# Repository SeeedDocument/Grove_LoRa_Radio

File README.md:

# Grove_LoRa_Radio
Grove LoRa Radio 433MHz SKU: 113060007

Grove LoRa Radio 868MHz SKU: 113060006

Change Log:

- 2016-11-27: create repos by Jiankai.li (jiankai.li@seeed.cc)

## About Seeed

Seeed is a hardware innovation platform for makers to grow inspirations into differentiating products. By working closely with technology providers of all scale, Seeed provides accessible technologies with quality, speed and supply chain knowledge. When prototypes are ready to iterate, Seeed helps productize 1 to 1,000 pcs using in-house engineering, supply chain management and agile manufacture forces. Seeed also team up with incubators, Chinese tech ecosystem, investors and distribution channels to portal Maker startups beyond.

## Contribution

We warmly welcome contribution to this documentation project. You can do this basically by [forking](https://help.github.com/articles/fork-a-repo), committing modifications and then [pulling requests](https://help.github.com/articles/using-pull-requests) (follow the links above for operating guide). Adding change log and your contact into file header is encouraged. Thanks for your contribution.

LICENSE
-------
Copyright (c) 2008-2016 Seeed Development Limited (www.seeedstudio.com / www.seeed.cc)

### Documents and Images
</a><br />
This work (product documents and associated images) are licensed under a <a rel="license" href="http://creativecommons.org/licenses/by-sa/4.0/">Creative Commons Attribution-ShareAlike 4.0 International License</a>. 

### Software Library
All demo software, code examples embedded in the document and any software libraray provided with the product document are licensed under [MIT License](https://github.com/SeeedDoc/WikiMigrationSync/blob/master/MIT_LICENSE "MIT LICENSE") unless otherwise specified.

### Thirdparty content
The resources provided with the product documents also contains datasheets, software examples and other content copyrighted by 3rd party authors and companies. All such items are copyright of respective owners. The use of such items are governed by their respective licenses.

All trademarks are the property of their respective owners.

### To Contact

Write to us at  with subject line "Wiki". Thanks

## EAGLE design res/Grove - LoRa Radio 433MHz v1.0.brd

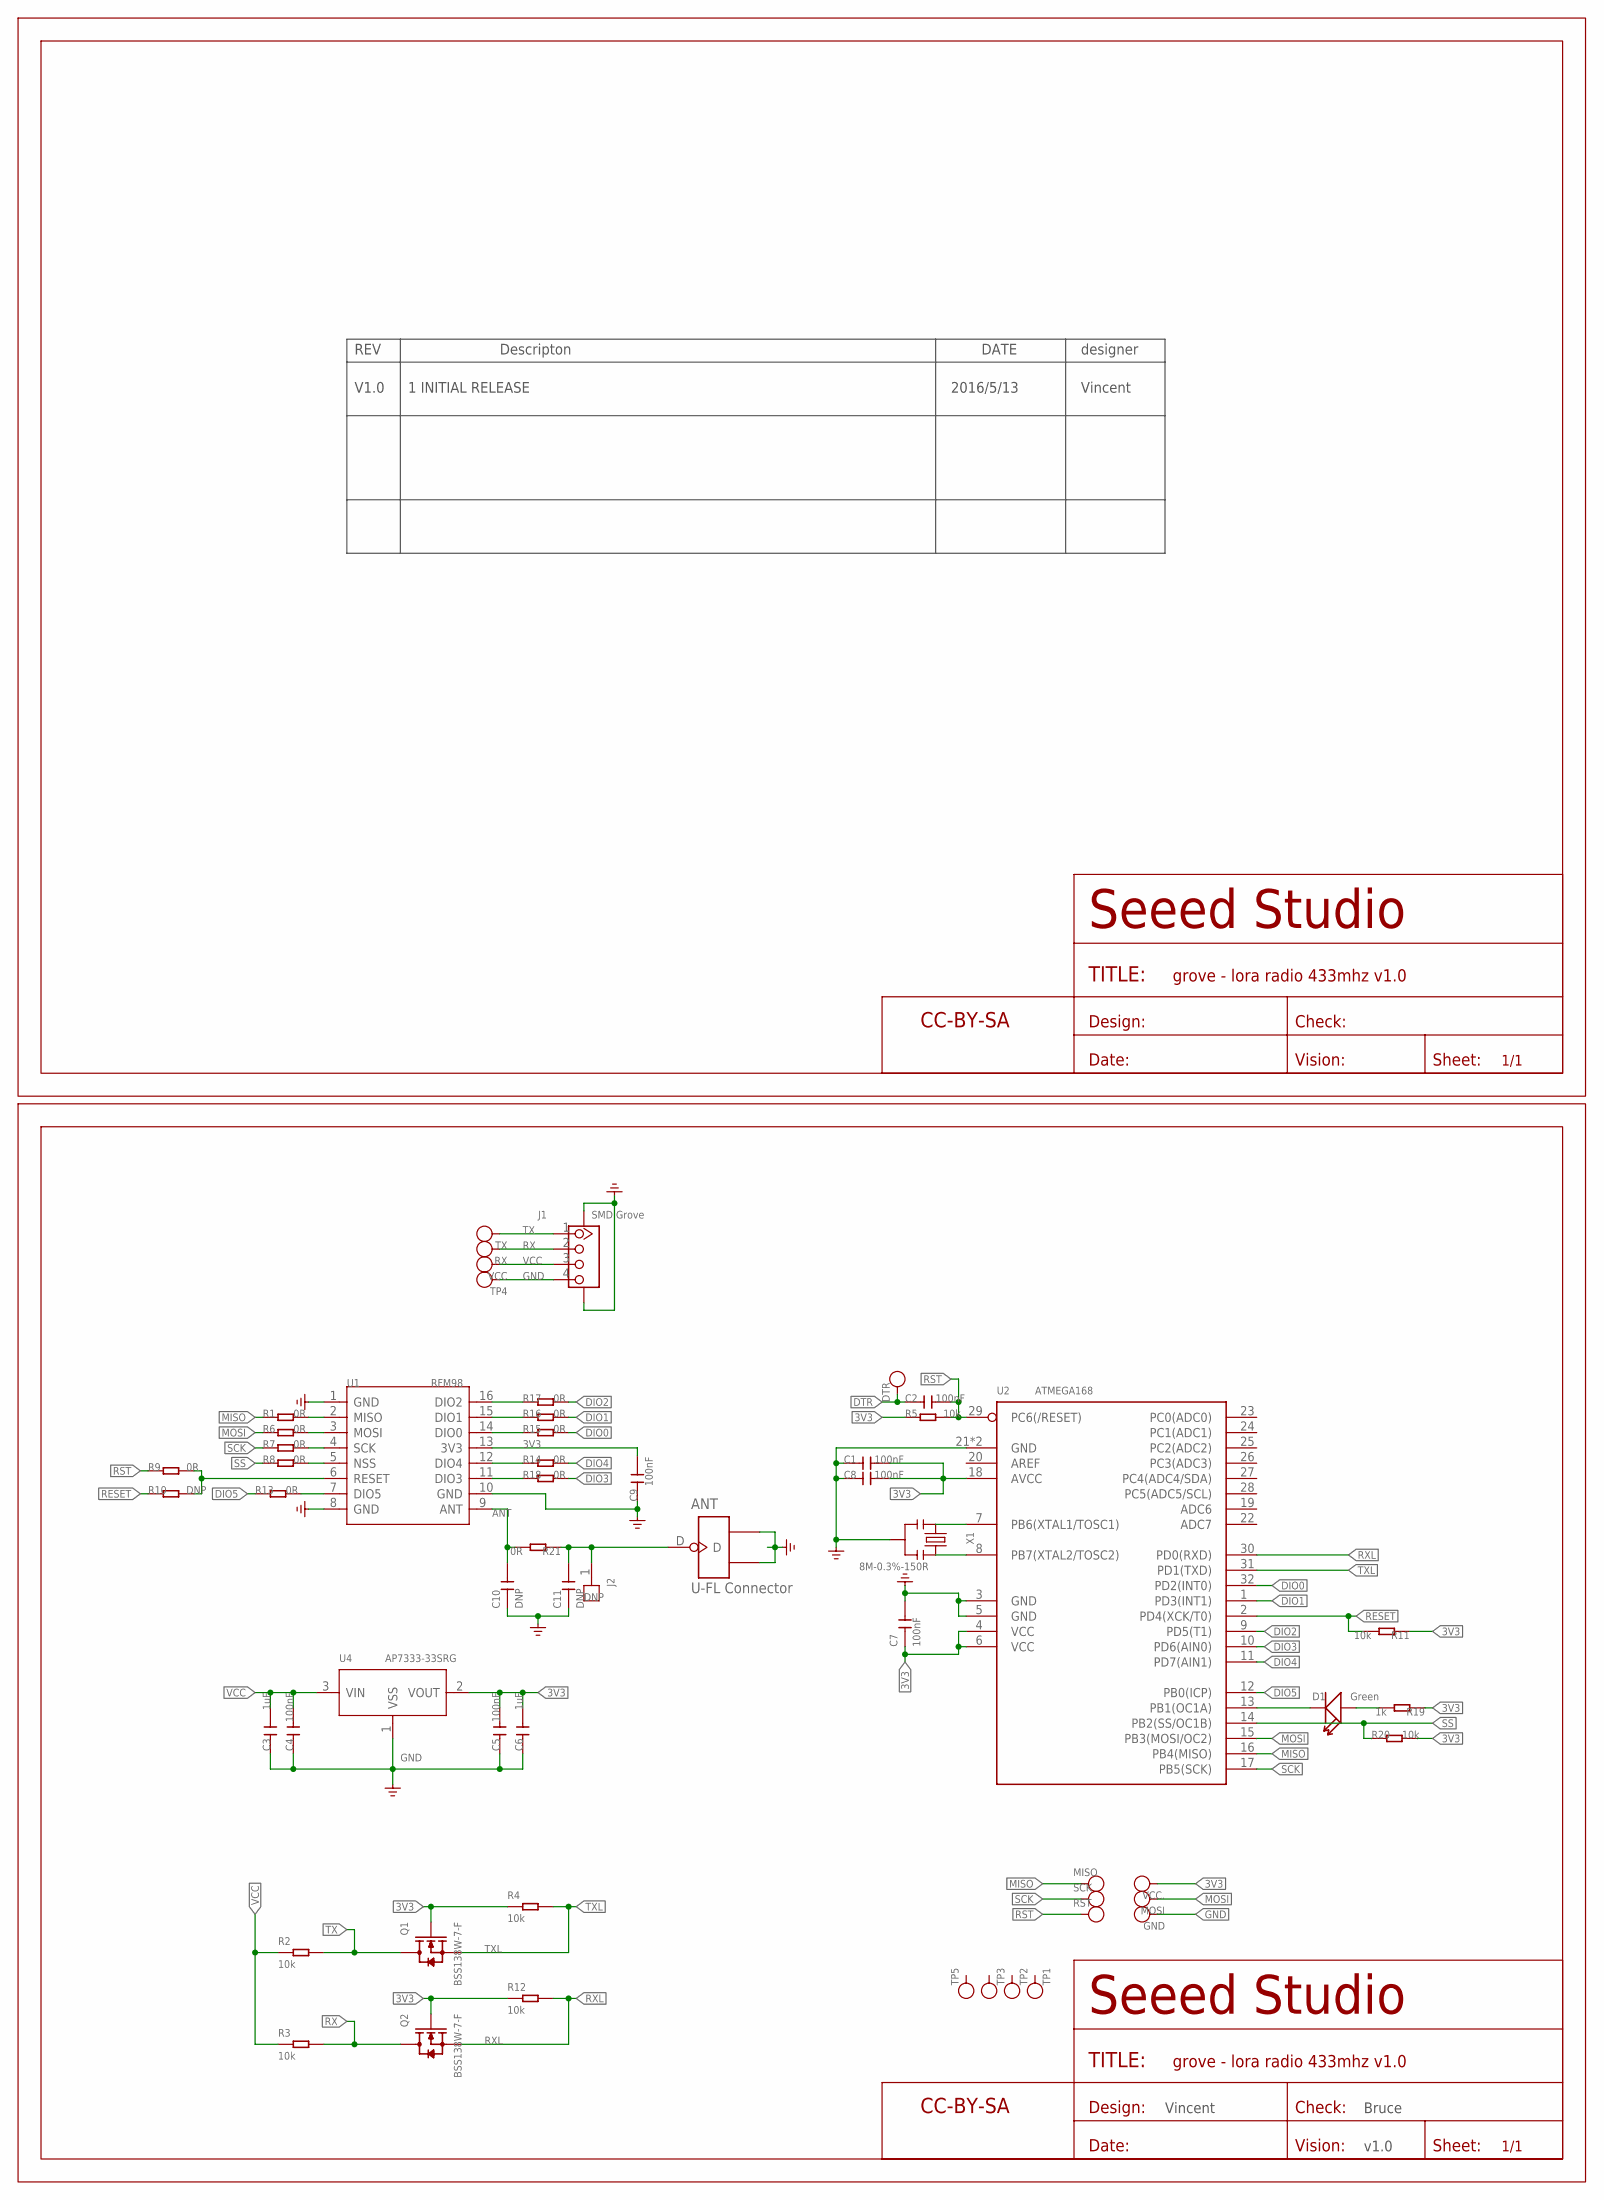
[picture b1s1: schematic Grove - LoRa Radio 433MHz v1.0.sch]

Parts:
ANT: U-FL Connector; U-FL3P-SMD-2.6X2.6X1.0MM
C1, C2, C4, C5, C7, C8, C9: 100nF; C0402
C3, C6: 1uF; C0402
C10, C11: DNP; C0402
D1: Green; LED-0402
DTR: TEST-POINT'4545'; TP-D45MIL
FR1, FR2: SEEEDSTUDIO-OPEN-SCH-FRAME; SEEEDSTUDIO-PCB-FRAME
GND: DNP; TP-D45MIL
J1: SMD Grove; HW4-SMD-2.0
J2: DNP; 1P-65/35MIL
MISO: DNP; TP-D45MIL
MOSI: DNP; TP-D45MIL
Q1, Q2: BSS138W-7-F; SOT-323
R1, R6, R7, R8, R9, R13, R14, R15, R16, R17, R18: 0R; R0402
R2, R3, R4, R5, R11, R12, R20: 10k; R0402
R10: DNP; R0402
R19: 1k; R0402
R21: 0R; R0603
RST: DNP; TP-D45MIL
RX: TEST-POINT'4545'; TP-D45MIL
SCK: DNP; TP-D45MIL
TP1, TP2, TP3, TP4, TP5: TEST-POINT'4545'; TP-D45MIL
TX: TEST-POINT'4545'; TP-D45MIL
U1: RFM98; MODEM16-2-16X16X1.8MM
U2: ATMEGA168; QFN32G-0.5-5X5MM
U4: AP7333-33SRG; SOT-23
VCC: TEST-POINT'4545'; TP-D45MIL
VCC.: NC; TP-D45MIL
X1: 8M-0.3%-150R; RESONATOR3-SMD-3.6X1.3X0.8MM

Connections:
3V3: C1.2, C5.1, C6.1, C7.1, C8.2, C9.2, Q1.1 (G), Q2.1 (G), R4.1, R5.2, R11.2, R12.1, R19.2, R20.2, U1.13 (3V3), U2.4 (VCC), U2.6 (VCC), U2.18 (AVCC), U4.2 (VOUT), VCC..T
ANT: C10.2, R21.2, U1.9 (ANT)
DIO0: R15.2, U2.32 (PD2(INT0))
DIO1: R16.2, U2.1 (PD3(INT1))
DIO2: R17.2, U2.9 (PD5(T1))
DIO3: R18.2, U2.10 (PD6(AIN0))
DIO4: R14.2, U2.11 (PD7(AIN1))
DIO5: R13.1, U2.12 (PB0(ICP))
DTR: C2.1, DTR.T
GND: ANT.GND1, ANT.GND2, C1.1, C3.2, C4.2, C5.2, C6.2, C7.2, C8.1, C9.1, C10.1, C11.1, GND.T, J1.4, J1.SS1, J1.SS2, TP4.T, U1.1 (GND), U1.8 (GND), U1.10 (GND), U2.3 (GND), U2.5 (GND), U2.21 (GND), U2.33 (GND), U4.1 (VSS), X1.2
MISO: MISO.T, R1.1, U2.16 (PB4(MISO))
MOSI: MOSI.T, R6.1, U2.15 (PB3(MOSI/OC2))
unnamed: R13.2, U1.7 (DIO5)
unnamed: R17.1, U1.16 (DIO2)
unnamed: R9.1, R10.1, U1.6 (RESET)
unnamed: R16.1, U1.15 (DIO1)
unnamed: R15.1, U1.14 (DIO0)
unnamed: R14.1, U1.12 (DIO4)
unnamed: R1.2, U1.2 (MISO)
unnamed: R6.2, U1.3 (MOSI)
unnamed: R7.2, U1.4 (SCK)
unnamed: R8.2, U1.5 (NSS)
unnamed: R18.1, U1.11 (DIO3)
unnamed: D1.-, U2.13 (PB1(OC1A))
unnamed: D1.+, R19.1
unnamed: ANT.D, C11.2, J2.1, R21.1
RESET: R10.2, R11.1, U2.2 (PD4(XCK/T0))
RST: C2.2, R5.1, R9.2, RST.T, U2.29 (PC6(/RESET))
RX: J1.2, Q2.3 (D), R3.2, RX.T
RXL: Q2.2 (S), R12.2, U2.30 (PD0(RXD))
SCK: R7.1, SCK.T, U2.17 (PB5(SCK))
SS: R8.1, R20.1, U2.14 (PB2(SS/OC1B))
TX: J1.1, Q1.3 (D), R2.2, TX.T
TXL: Q1.2 (S), R4.2, U2.31 (PD1(TXD))
VCC: C3.1, C4.1, J1.3, R2.1, R3.1, U4.3 (VIN), VCC.T
XTAL1: U2.7 (PB6(XTAL1/TOSC1)), X1.1
XTAL2: U2.8 (PB7(XTAL2/TOSC2)), X1.3

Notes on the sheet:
REV
Descripton
DATE
designer
V1.0
1 INITIAL RELEASE
2016/5/13
Vincent
Bruce
v1.0

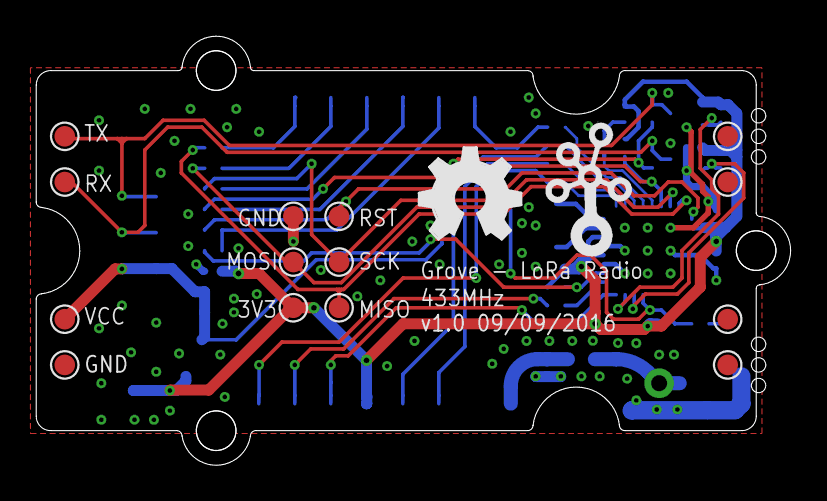
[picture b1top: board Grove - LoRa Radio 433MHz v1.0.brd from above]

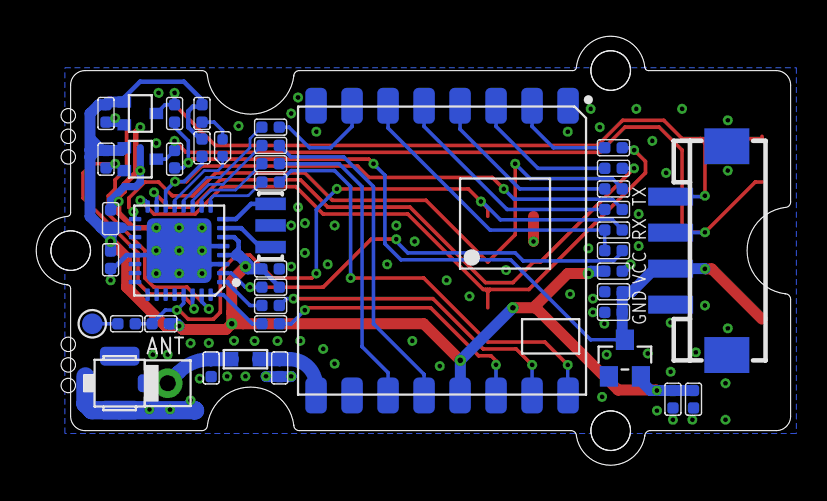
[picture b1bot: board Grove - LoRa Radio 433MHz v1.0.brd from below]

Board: 2 copper layers, 41.9 x 23.8 mm, 62 parts (46 on the bottom side), 37 nets.

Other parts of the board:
U$2: OSHW_FILLX200_NOTEXT
U$4: GROVE-1*2-TEST-PLATFORM-TOP
U$8: GROVE-SILK-BIG

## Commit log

2016-11-27 add the res
2016-11-27 finish the readme file
2016-11-27 add some image
2016-11-27 add res
2016-11-27 finish the wiki
2016-12-13 update cover
2016-12-13 add image to download library
2016-12-13 add open examples image
2016-12-13 update image
2016-12-13 update hardware overview image
2016-12-13 add Atmega168 datasheet
2016-12-13 add res all
2016-12-13 update resources
2016-12-13 rename resources

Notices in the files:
README.md:
CC BY-SA 4.0
parts and their libraries:
moudle-new: This work is licensed under the Creative Commons Attribution 4.0 International License.
To view a copy of this license,visit: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
moudle-new: CC-BY-SA
